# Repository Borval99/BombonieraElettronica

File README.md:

# Bomboniera Elettronica

## Descrizione

BombonieraElettronica è una bomboniera realizzata in occasione della tesi di Laurea Magistrale in Ingegneria Elettronica.

Il dispositivo è basato su un circuito stampato (PCB) che integra una semplice logica elettronica per la generazione di un effetto luminoso.

---

## Funzionamento

La bomboniera è dotata di un **interruttore touch**, integrato nel cappello di laurea, che consente di attivare e disattivare il circuito.

Il sistema di illuminazione è realizzato tramite un **multivibratore astabile a BJT**, che genera un segnale oscillante utilizzato per pilotare 5 Led gialli.

Il risultato è un gioco di luci intermittente.

L’alimentazione è fornita da una **batteria CR2032**, rendendo il dispositivo compatto e autonomo. La durata da spento è stimata di circa 2 Anni.

---

## Immagini

<div>

</div>

---

## Struttura della repository

### /Bomboniera_Tesi

Contiene il progetto elettronico completo realizzato in KiCad:

* schema elettrico
* layout del PCB

---

### /LTspice

Contiene le simulazioni dei circuiti sviluppati:

* modelli del multivibratore astabile
* analisi del comportamento del circuito

---

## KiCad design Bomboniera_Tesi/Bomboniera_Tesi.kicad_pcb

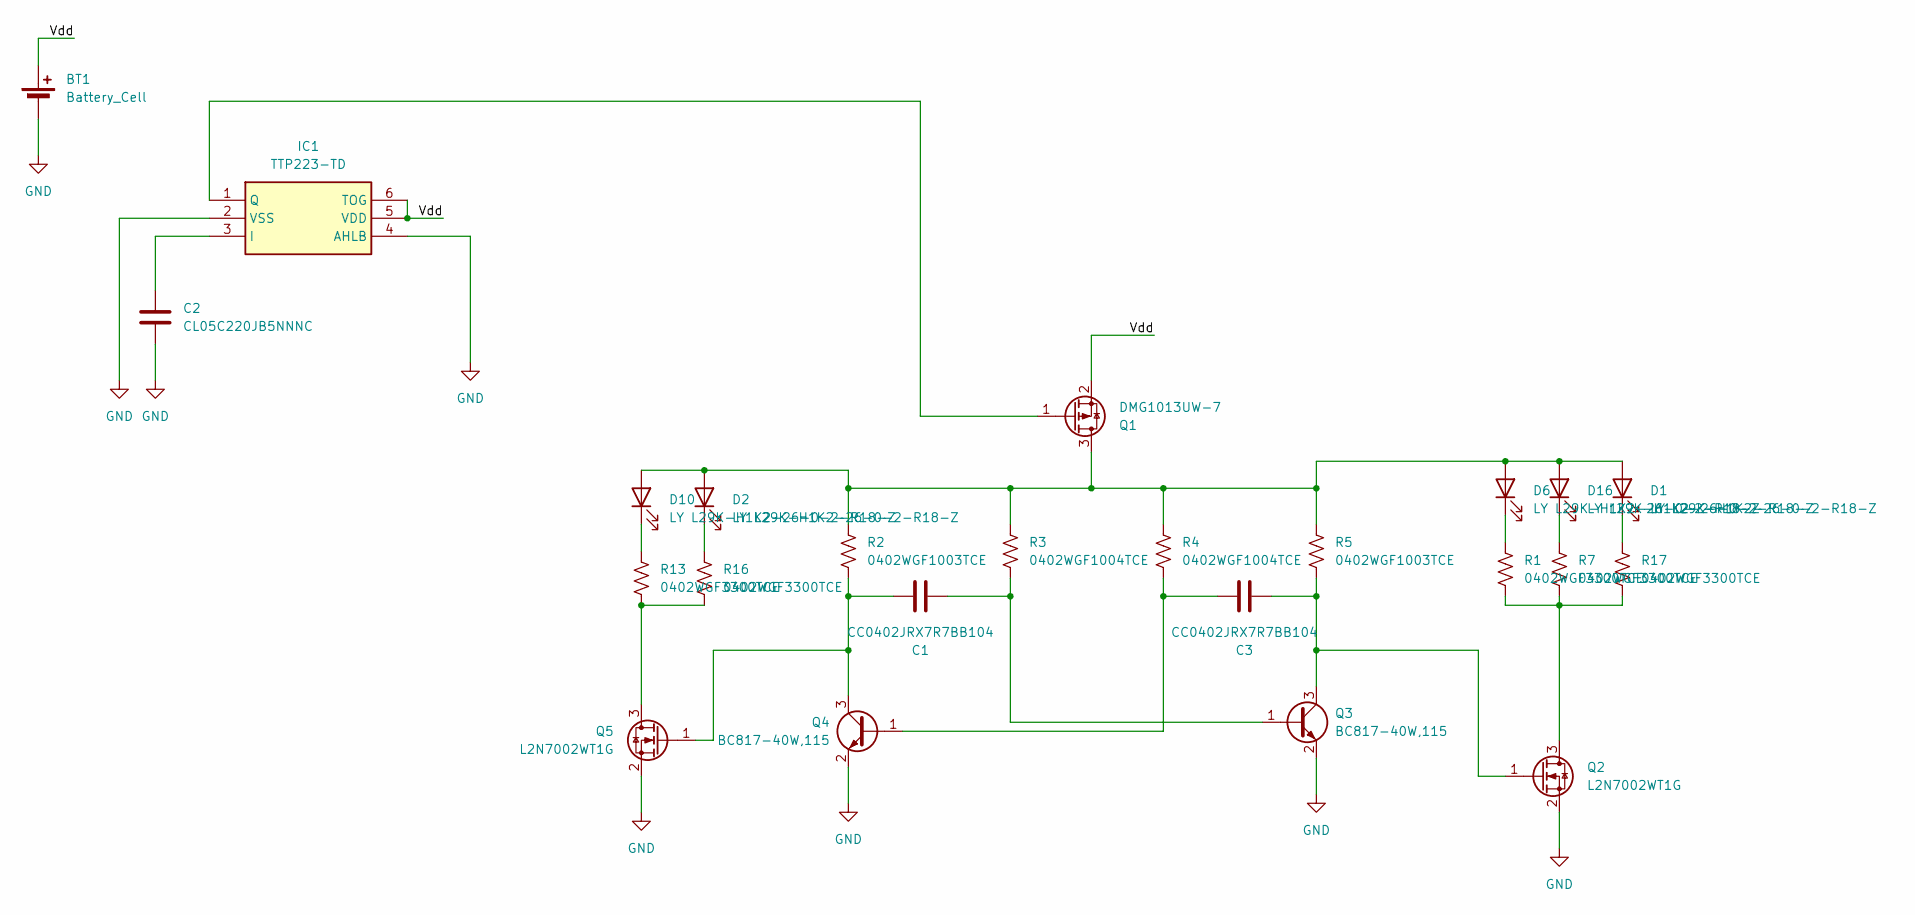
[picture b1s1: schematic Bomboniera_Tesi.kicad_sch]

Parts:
BT1: Battery_Cell; BatteryHolder_Keystone_1060_1x2032
C1, C3: CC0402JRX7R7BB104; C_0402_1005Metric
C2: CL05C220JB5NNNC; C_0402_1005Metric
D1, D2, D6, D10, D16: LY L29K-H1K2-26-0-2-R18-Z; LED_LY L29K_MUR
IC1: TTP223-TD; SOT95P285X126-6N
Q1: DMG1013UW-7; SOT-323_SC-70
Q2, Q5: L2N7002WT1G; SOT-323_SC-70
Q3, Q4: BC817-40W,115; SOT-323_SC-70
R1, R7, R13, R16, R17: 0402WGF3300TCE; R_0402_1005Metric
R2, R5: 0402WGF1003TCE; R_0402_1005Metric
R3, R4: 0402WGF1004TCE; R_0402_1005Metric

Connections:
/Vdd: BT1.1 (+), IC1.5 (VDD), IC1.6 (TOG), Q1.2 (S)
GND: BT1.2 (-), C2.2, IC1.2 (VSS), IC1.4 (AHLB), Q2.2 (S), Q3.2 (E), Q4.2 (E), Q5.2 (S)
unnamed: D1.2 (A), D2.2 (A), D6.2 (A), D10.2 (A), D16.2 (A), Q1.3 (D), R2.1, R3.1, R4.2, R5.1
unnamed: D1.1 (K), R17.1
unnamed: D2.1 (K), R16.1
unnamed: D6.1 (K), R1.1
unnamed: D10.1 (K), R13.1
unnamed: D16.1 (K), R7.1
unnamed: C2.1, IC1.3 (I)
unnamed: IC1.1 (Q), Q1.1 (G)
unnamed: Q2.3 (D), R1.2, R7.2, R17.2
unnamed: C3.2, Q2.1 (G), Q3.3 (C), R5.2
unnamed: C1.2, Q3.1 (B), R3.2
unnamed: C3.1, Q4.1 (B), R4.1
unnamed: C1.1, Q4.3 (C), Q5.1 (G), R2.2
unnamed: Q5.3 (D), R13.2, R16.2

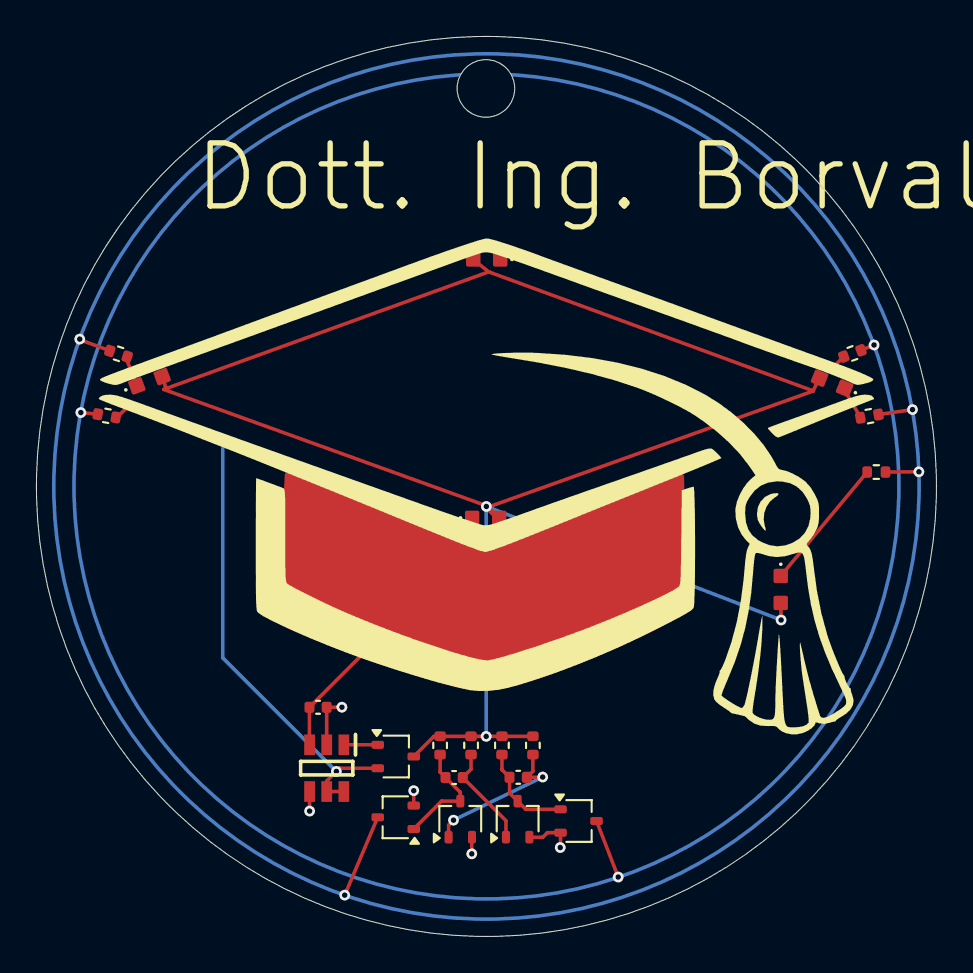
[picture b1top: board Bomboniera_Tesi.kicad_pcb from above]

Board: 2 copper layers, 50.0 x 50.0 mm, 24 parts (1 on the bottom side), 16 nets.

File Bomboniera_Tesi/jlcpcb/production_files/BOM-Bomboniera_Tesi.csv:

Comment,Designator,Footprint,LCSC,Quantity
0402WGF1003TCE,"R2,R5",R_0402_1005Metric,C25741,2
0402WGF1004TCE,"R3,R4",R_0402_1005Metric,C26083,2
"BC817-40W,115","Q3,Q4",SOT-323_SC-70,C53113961,2
CC0402JRX7R7BB104,"C1,C3",C_0402_1005Metric,C541464,2
CL05C220JB5NNNC,C2,C_0402_1005Metric,C70464,1
DMG1013UW-7,Q1,SOT-323_SC-70,C211434,1
L2N7002WT1G,"Q2,Q5",SOT-323_SC-70,C12778,2
LY L29K-H1K2-26-0-2-R18-Z,"D1,D10,D16,D2,D6",LED_LY L29K_MUR,C2900144,5
TTP223-TD,IC1,SOT95P285X126-6N,C42422128,1
0402WGF3300TCE,R17,R_0402_1005Metric,,1
0402WGF3300TCE,R13,R_0402_1005Metric,,1
0402WGF3300TCE,R16,R_0402_1005Metric,,1
0402WGF3300TCE,R1,R_0402_1005Metric,,1
0402WGF3300TCE,R7,R_0402_1005Metric,,1

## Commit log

2026-04-02 Massive Update
